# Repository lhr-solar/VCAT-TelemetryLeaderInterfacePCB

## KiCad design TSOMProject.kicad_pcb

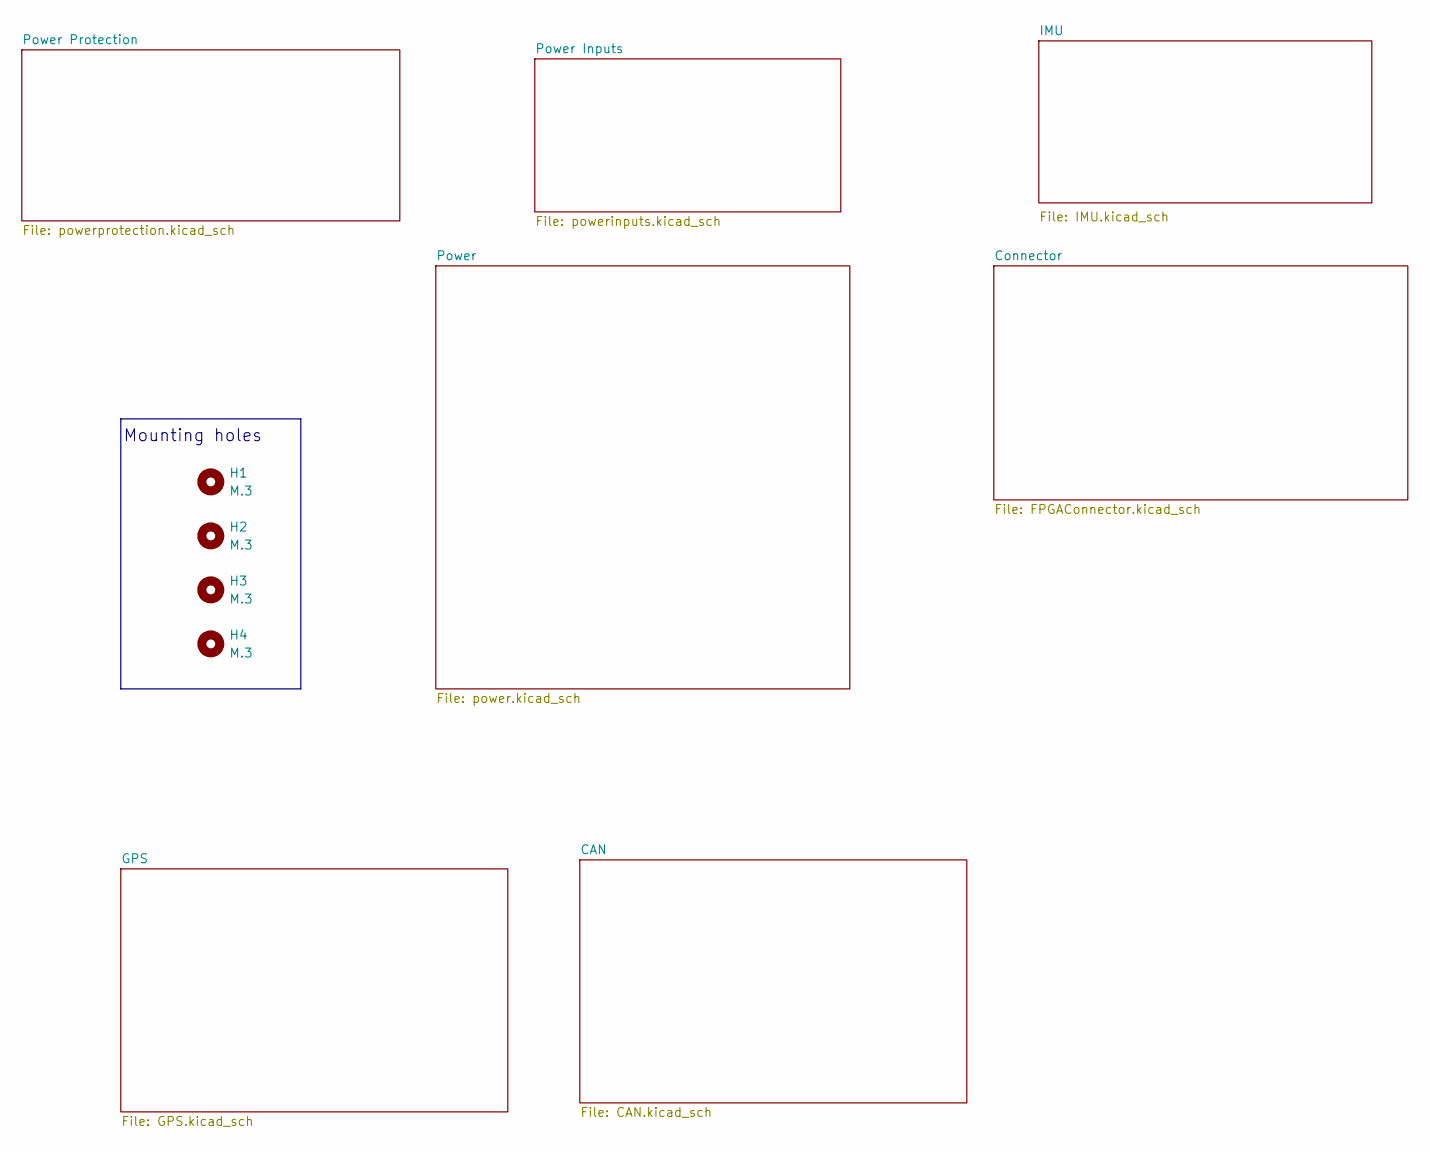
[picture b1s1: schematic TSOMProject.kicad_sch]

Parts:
H1, H2, H3, H4: M.3; MountingHole_3mm

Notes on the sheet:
Mounting holes

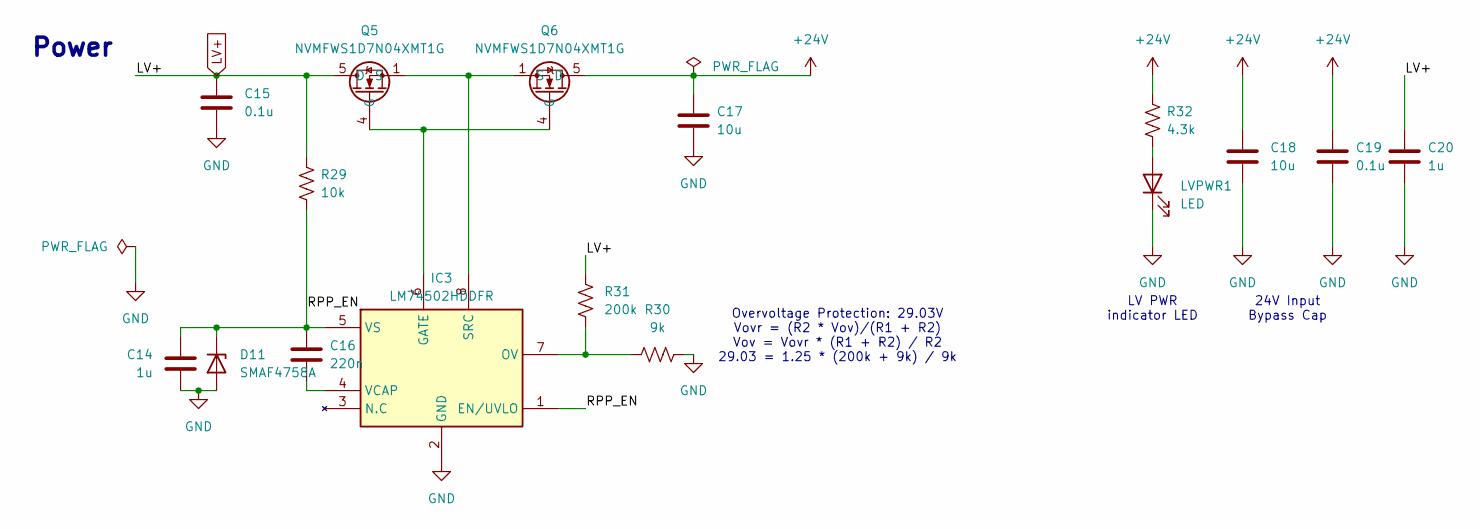
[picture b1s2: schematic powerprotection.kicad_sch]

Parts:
C14: 1u; C_0603_1608Metric_Pad1.08x0.95mm_HandSolder; Mouser Part Number 963-UMK107BJ105KA-T
C15, C19: 0.1u; C_0603_1608Metric_Pad1.08x0.95mm_HandSolder; Mouser Part Number 963-HMK107B7104KA-T
C16: 220n; C_0603_1608Metric_Pad1.08x0.95mm_HandSolder; Mouser Part Number 963-MSASU168SB7224KT
C17, C18: 10u; C_0805_2012Metric_Pad1.18x1.45mm_HandSolder; Mouser Part Number 81-GRM21BR61H106KE3K
C20: 1u; C_0603_1608Metric_Pad1.08x0.95mm_HandSolder; Mouser Part Number 963-HMK107B7104KA-T
D11: SMAF4758A; SODFL5026X125N; Mouser Part Number 833-SMAF4758A-TP
IC3: LM74502HDDFR; SOT65P280X110-8N; Mouser Part Number 595-LM74502HDDFR
LVPWR1: LED; LED_0603_1608Metric_Pad1.05x0.95mm_HandSolder; LCSC C7371904
Q5, Q6: NVMFWS1D7N04XMT1G; NVMFWS3D0P04M8LT1G; LCSC C133142
R29: 10k; R_0603_1608Metric_Pad0.98x0.95mm_HandSolder; Mouser Part Number 71-CRCW060310K0FKEI
R30: 9k; R_0603_1608Metric_Pad0.98x0.95mm_HandSolder; Mouser Part Number 594-MCT06030C9091FP5
R31: 200k; R_0603_1608Metric_Pad0.98x0.95mm_HandSolder; Mouser Part Number 594-MCT06030C2003FP5
R32: 4.3k; R_0603_1608Metric_Pad0.98x0.95mm_HandSolder; Mouser Part Number 71-CRCW0603-4.3K-E3

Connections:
+24V: C17.1, C18.1, C19.1, Q6.5 (D), Q6.6 (D), Q6.7 (D), Q6.8 (D), Q6.9 (D), R32.1; also elsewhere on the board
/Power Protection/RPP_EN: C14.2, C16.1, D11.1 (K), IC3.1 (EN/UVLO), IC3.5 (VS), R29.2
GND: C14.1, C15.2, C17.2, C18.2, C19.2, C20.2, D11.2 (A), IC3.2 (GND), LVPWR1.1 (K), R30.2; also elsewhere on the board
LV+: C15.1, C20.1, Q5.5 (D), Q5.6 (D), Q5.7 (D), Q5.8 (D), Q5.9 (D), R29.1, R31.1; also elsewhere on the board
unnamed: IC3.6 (GATE), Q5.4 (G), Q6.4 (G)
unnamed: IC3.7 (OV), R30.1, R31.2
unnamed: IC3.8 (SRC), Q5.1 (S), Q5.2 (S), Q5.3 (S), Q6.1 (S), Q6.2 (S), Q6.3 (S)
unnamed: C16.2, IC3.4 (VCAP)
unnamed: LVPWR1.2 (A), R32.2

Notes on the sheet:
24V Input Bypass Cap
LV PWR indicator LED
Overvoltage Protection: 29.03V Vovr = (R2 * Vov)/(R1 + R2) Vov = Vovr * (R1 + R2) / R2 29.03 = 1.25 * (200k + 9k) / 9k
Power

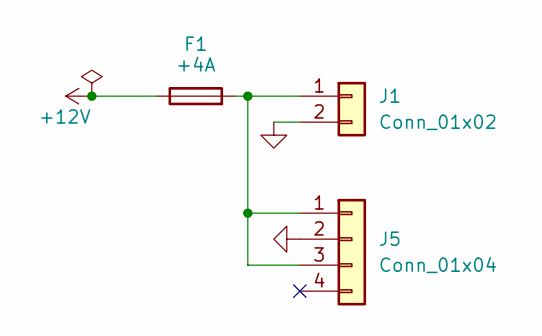
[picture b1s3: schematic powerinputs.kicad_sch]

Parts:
F1: +4A; Fuseholder_Blade_Mini_Keystone_3568
J1: Conn_01x02; Molex_Nano-Fit_105309-xx02_1x02_P2.50mm_Vertical
J5: Conn_01x04; Molex_Nano-Fit_105310-xx04_2x02_P2.50mm_Vertical

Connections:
+12V: F1.1; also elsewhere on the board
GND: J1.2, J5.2; also elsewhere on the board
unnamed: F1.2, J1.1, J5.1, J5.3

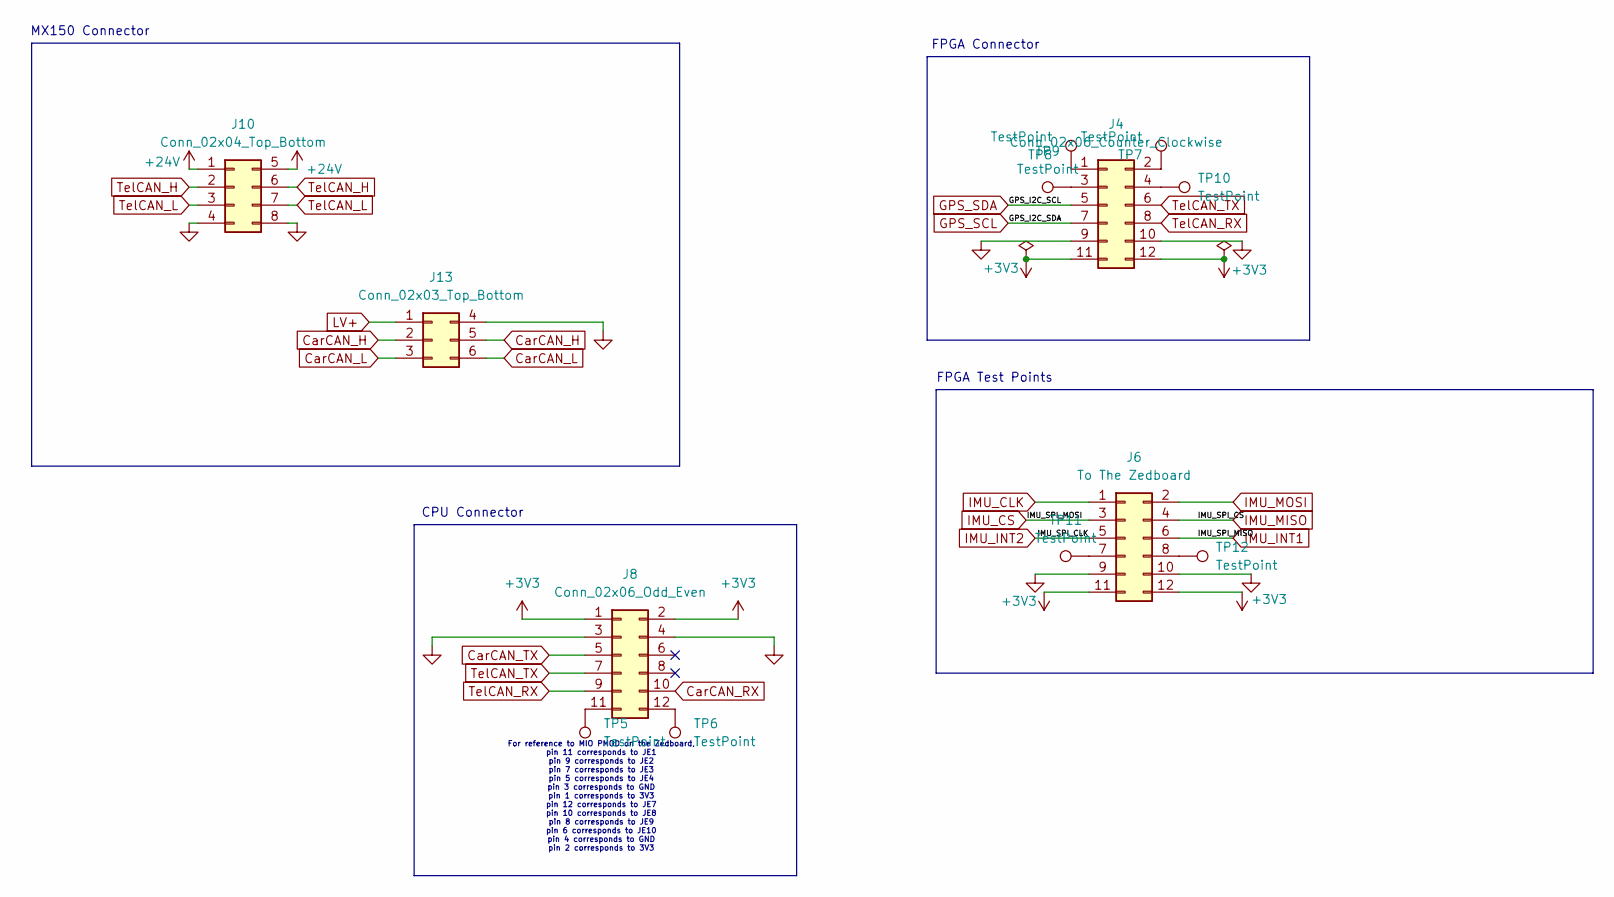
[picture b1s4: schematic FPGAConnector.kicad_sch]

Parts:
J4: Conn_02x06_Counter_Clockwise; PinHeader_2x06_P2.54mm_Vertical
J6: To The Zedboard; 2x6PmodConnectorWithZedboard
J8: Conn_02x06_Odd_Even; PinHeader_2x06_P2.54mm_Vertical
J10: Conn_02x04_Top_Bottom; Molex_Nano-Fit_105310-xx08_2x04_P2.50mm_Vertical
J13: Conn_02x03_Top_Bottom; Molex_Nano-Fit_105310-xx06_2x03_P2.50mm_Vertical
TP5, TP6, TP7, TP8, TP9, TP10, TP11, TP12: TestPoint; TestPoint_THTPad_D2.0mm_Drill1.0mm

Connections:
+3V3: J4.11, J4.12, J6.11, J6.12, J8.1, J8.2; also elsewhere on the board
+24V: J10.1, J10.5; also elsewhere on the board
CarCAN_H: J13.2, J13.5; also elsewhere on the board
CarCAN_L: J13.3, J13.6; also elsewhere on the board
CarCAN_RX: J8.10; also elsewhere on the board
CarCAN_TX: J8.5; also elsewhere on the board
GND: J4.9, J4.10, J6.9, J6.10, J8.3, J8.4, J10.4, J10.8, J13.4; also elsewhere on the board
GPS_SCL: J4.7; also elsewhere on the board
GPS_SDA: J4.5; also elsewhere on the board
IMU_CLK: J6.1; also elsewhere on the board
IMU_CS: J6.3 (Pin_2); also elsewhere on the board
IMU_INT1: J6.6; also elsewhere on the board
IMU_INT2: J6.5; also elsewhere on the board
IMU_MISO: J6.4; also elsewhere on the board
IMU_MOSI: J6.2; also elsewhere on the board
LV+: J13.1; also elsewhere on the board
unnamed: J4.1, TP8.1
unnamed: J4.2, TP7.1
unnamed: J4.3, TP9.1
unnamed: J4.4, TP10.1
unnamed: J6.7, TP11.1
unnamed: J6.8, TP12.1
unnamed: J8.11, TP5.1
unnamed: J8.12, TP6.1
TelCAN_H: J10.2, J10.6; also elsewhere on the board
TelCAN_L: J10.3, J10.7; also elsewhere on the board
TelCAN_RX: J4.8, J8.9; also elsewhere on the board
TelCAN_TX: J4.6, J8.7; also elsewhere on the board

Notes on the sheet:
MX150 Connector
CPU Connector
FPGA Test Points
For reference to MIO PMOD on the Zedboard, pin 11 corresponds to JE1 pin 9 corresponds to JE2 pin 7 corresponds to JE3 pin 5 corresponds to JE4 pin 3 corresponds to GND pin 1 corresponds to 3V3 pin 12 corresponds to JE7 pin 10 corresponds to JE8 pin 8 corresponds to JE9 pin 6 corresponds to JE10 pi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
FPGA Connector

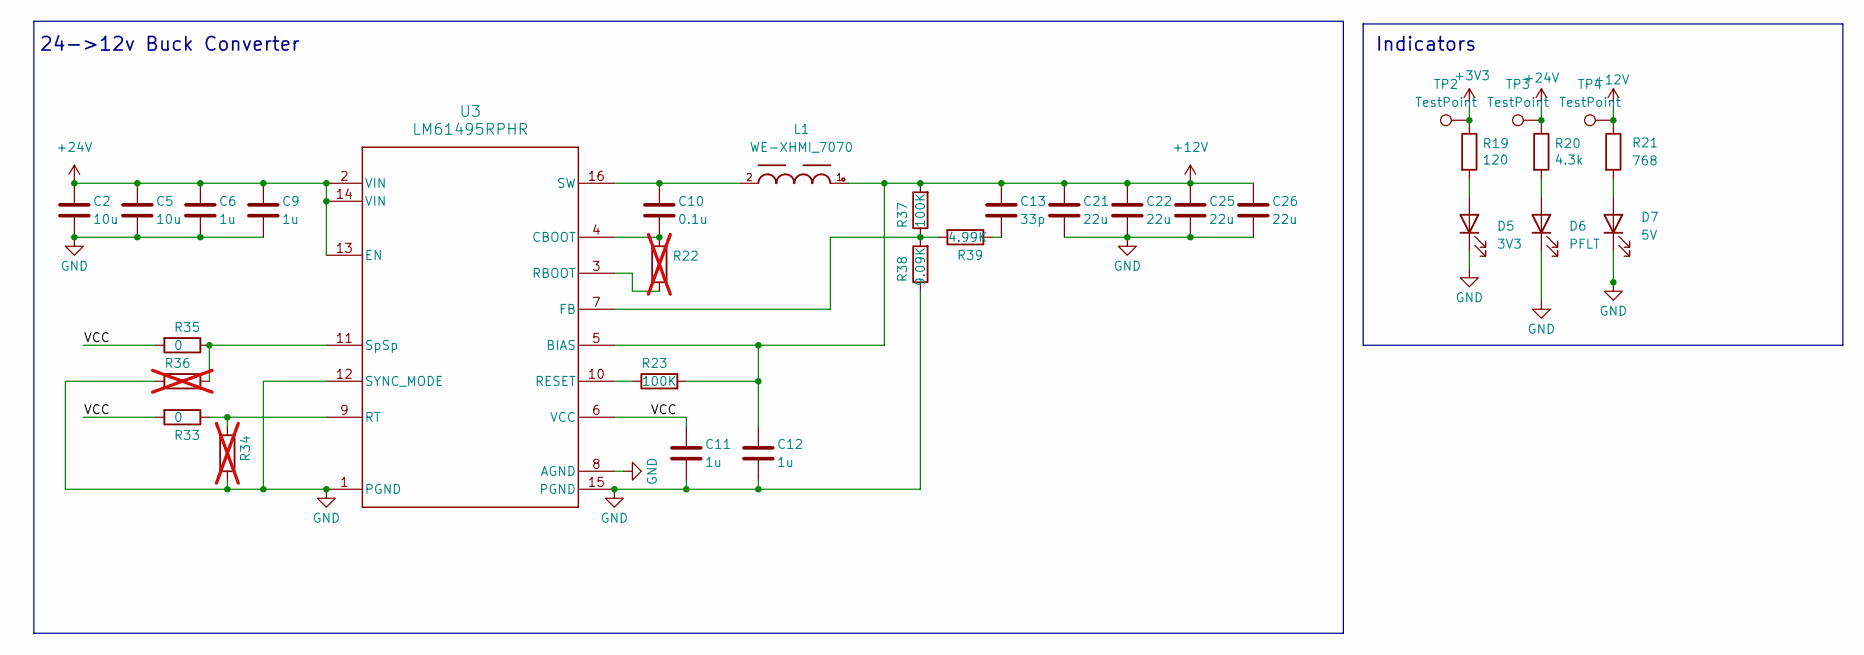
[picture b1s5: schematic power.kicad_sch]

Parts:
C2, C5: 10u; C_1206_3216Metric_Pad1.33x1.80mm_HandSolder; LCSC C7302214
C6, C9, C11, C12: 1u; C_0603_1608Metric_Pad1.08x0.95mm_HandSolder; LCSC C15849
C10: 0.1u; C_0603_1608Metric_Pad1.08x0.95mm_HandSolder; LCSC C14663
C13: 33p; C_0603_1608Metric_Pad1.08x0.95mm_HandSolder; LCSC C1663
C21, C22, C25, C26: 22u; C_1210_3225Metric_Pad1.33x2.70mm_HandSolder; LCSC C21397
D5: 3V3; LED_0603_1608Metric_Pad1.05x0.95mm_HandSolder; Mouser Part Number XL-1608UBC-06A
D6: PFLT; LED_0603_1608Metric_Pad1.05x0.95mm_HandSolder; Mouser Part Number XL-1608UBC-06A
D7: 5V; LED_0603_1608Metric_Pad1.05x0.95mm_HandSolder; Mouser Part Number XL-1608UBC-06A
L1: WE-XHMI_7070
R19: 120; R_0603_1608Metric_Pad0.98x0.95mm_HandSolder; Mouser Part Number CRCW0603120RFKEC
R20: 4.3k; R_0603_1608Metric_Pad0.98x0.95mm_HandSolder; Mouser Part Number CRCW06034K30FKTA
R21: 768; R_0603_1608Metric_Pad0.98x0.95mm_HandSolder; Mouser Part Number CRCW0603768RFKEA
R22, R34, R36: R_0603_1608Metric_Pad0.98x0.95mm_HandSolder; Mouser Part Number CRCW0603120RFKEC; not fitted
R23, R37: 100K; R_0603_1608Metric_Pad0.98x0.95mm_HandSolder; Mouser Part Number CRCW0603120RFKEC
R33, R35: 0; R_0603_1608Metric_Pad0.98x0.95mm_HandSolder; Mouser Part Number CRCW0603120RFKEC
R38: 9.09K; R_0603_1608Metric_Pad0.98x0.95mm_HandSolder; Mouser Part Number CRCW0603120RFKEC
R39: 4.99K; R_0603_1608Metric_Pad0.98x0.95mm_HandSolder; Mouser Part Number CRCW0603120RFKEC
TP2, TP3, TP4: TestPoint; TestPoint_THTPad_D2.0mm_Drill1.0mm
U3: LM61495RPHR; LCSC C2943584

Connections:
+3V3: R19.1, TP2.1; also elsewhere on the board
+12V: C12.1, C13.1, C21.1, C22.1, C25.1, C26.1, L1.1, R21.1, R23.2, R37.2, TP4.1, U3.5 (BIAS); also elsewhere on the board
+24V: C2.1, C5.1, C6.1, C9.1, R20.1, TP3.1, U3.2 (VIN), U3.13 (EN), U3.14 (VIN); also elsewhere on the board
/Power/VCC: C11.1, R33.2, R35.2, U3.6 (VCC)
GND: C2.2, C5.2, C6.2, C9.2, C11.2, C12.2, C21.2, C22.2, C25.2, C26.2, D5.1 (K), D6.1 (K), D7.1 (K), R34.2, R36.1, R38.1, U3.1 (PGND), U3.8 (AGND), U3.12 (SYNC_MODE), U3.15 (PGND); also elsewhere on the board
unnamed: C13.2, R39.1
unnamed: D5.2 (A), R19.2
unnamed: D6.2 (A), R20.2
unnamed: D7.2 (A), R21.2
unnamed: C10.2, R22.1, U3.4 (CBOOT)
unnamed: R37.1, R38.2, R39.2, U3.7 (FB)
unnamed: R22.2, U3.3 (RBOOT)
unnamed: R23.1, U3.10 (RESET)
unnamed: R33.1, R34.1, U3.9 (RT)
unnamed: C10.1, L1.2, U3.16 (SW)
unnamed: R35.1, R36.2, U3.11 (SpSp)

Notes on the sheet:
Indicators
24->12v Buck Converter

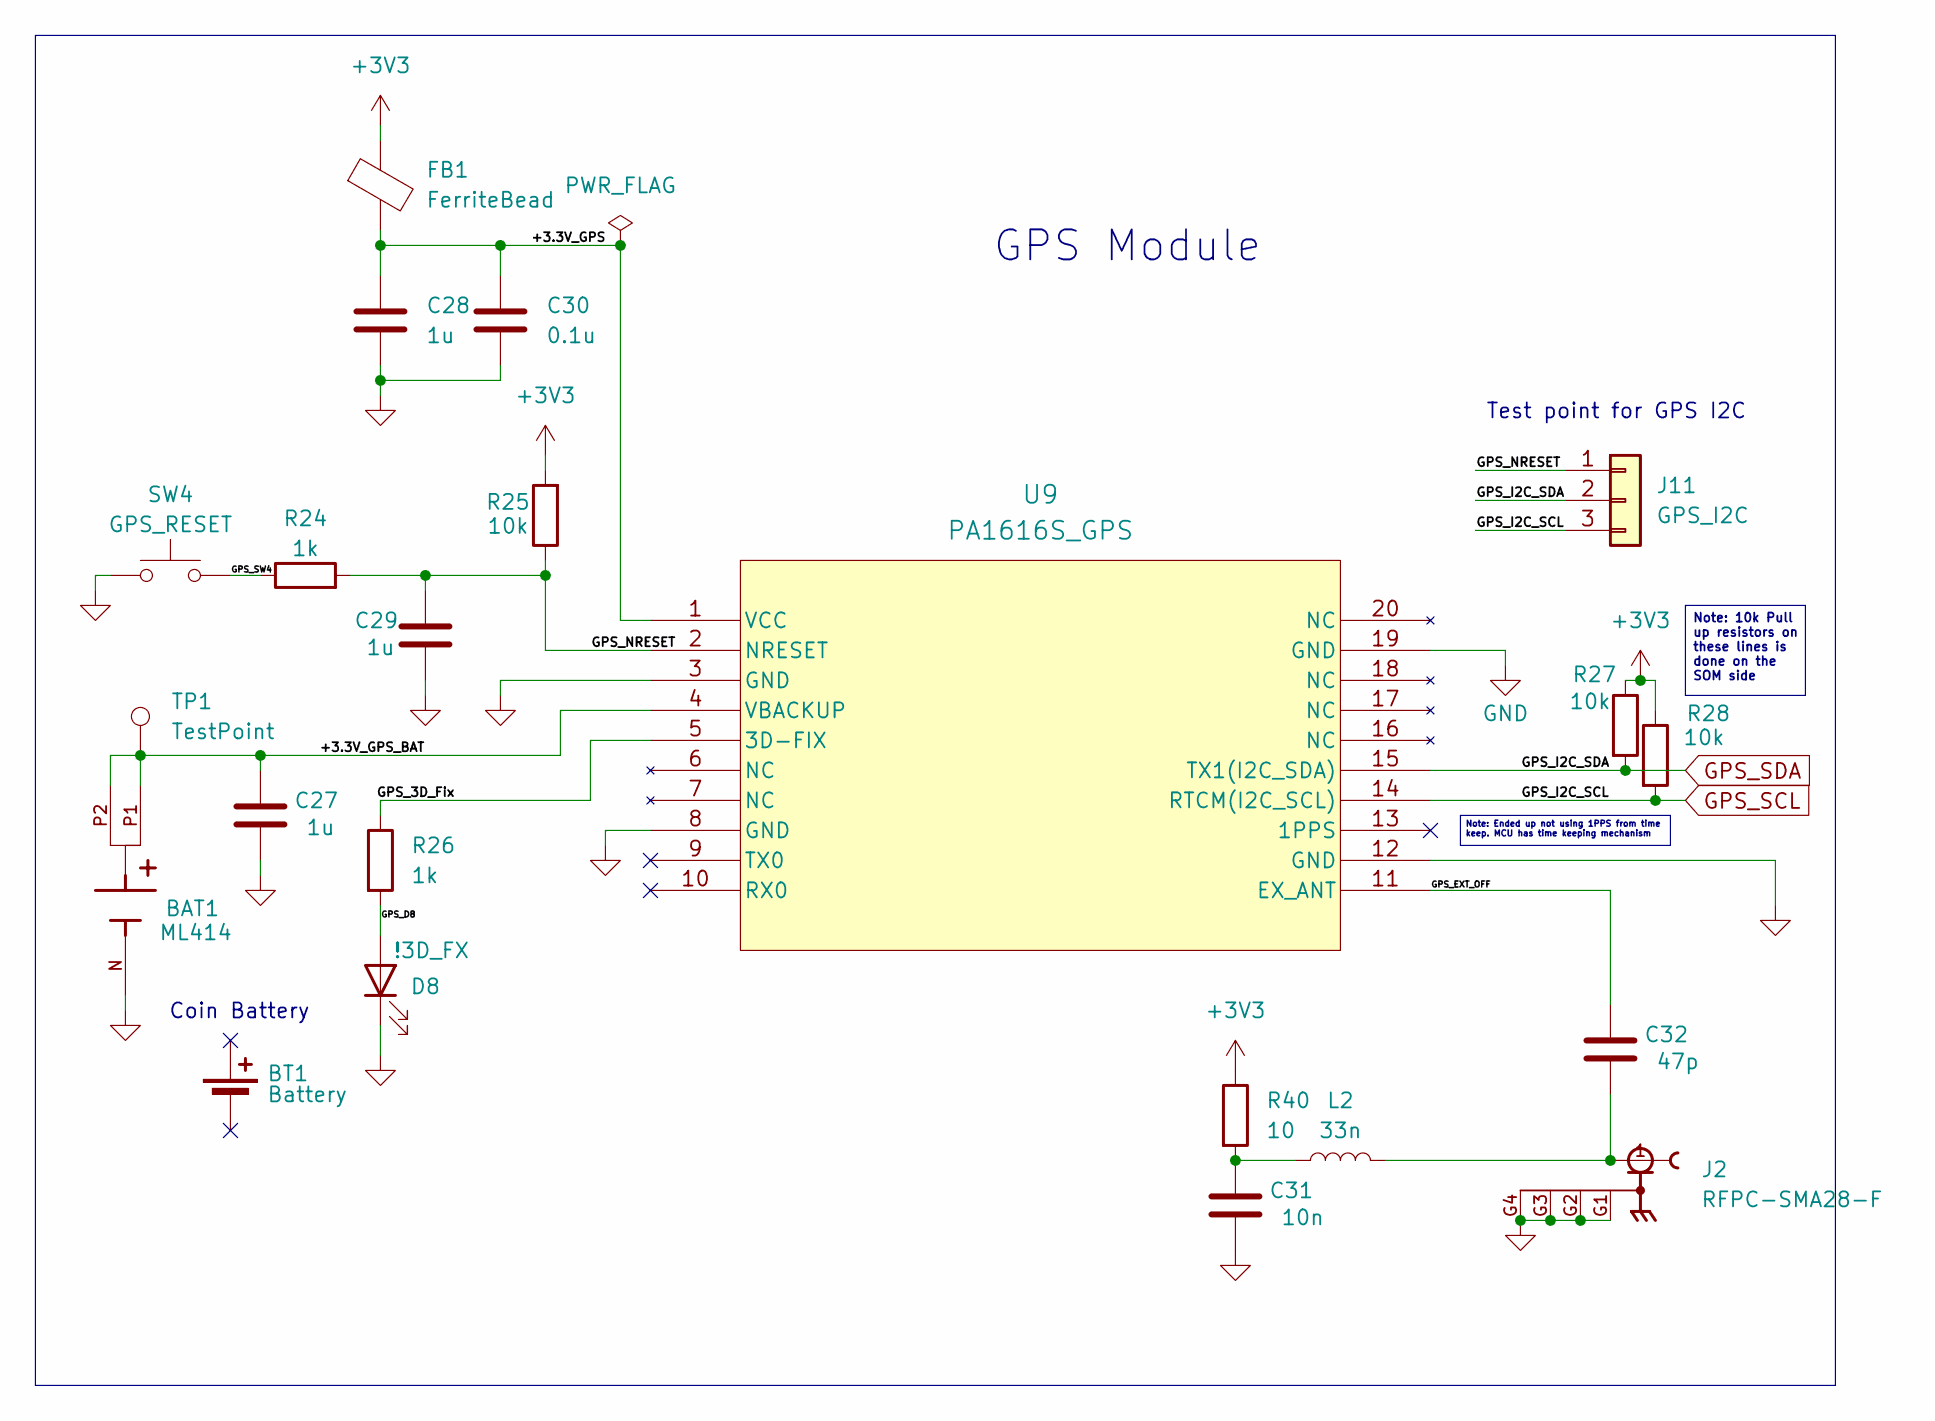
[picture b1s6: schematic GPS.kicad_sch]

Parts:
BAT1: ML414; BAT_2994TR; Mouser Part Number 534-2994TR
BT1: Battery; NA; Mouser Part Number 628-MS414GE
C27, C28, C29: 1u; C_0603_1608Metric_Pad1.08x0.95mm_HandSolder; Mouser Part Number 80-C0805C105J4RACLR
C30: 0.1u; C_0603_1608Metric_Pad1.08x0.95mm_HandSolder; Mouser Part Number 80-C0805C104M5R
C31: 10n; C_0603_1608Metric_Pad1.08x0.95mm_HandSolder; Mouser Part Number 80-C0805C105J4RACLR
C32: 47p; C_0603_1608Metric_Pad1.08x0.95mm_HandSolder; Mouser Part Number 80-C0805C105J4RACLR
D8: !3D_FX; LED_0603_1608Metric_Pad1.05x0.95mm_HandSolder; Mouser Part Number 604-APTD2012LCGCK
FB1: FerriteBead; L_0603_1608Metric_Pad1.05x0.95mm_HandSolder; Mouser Part Number 81-BLM15BD601SN1D
J2: RFPC-SMA28-F; GRADCONN_RFPC-SMA28-F; PARTREV 1.0
J11: GPS_I2C; PinHeader_1x03_P2.54mm_Vertical; Mouser Part Number 538-22-28-4035
L2: 33n; L_0603_1608Metric_Pad1.05x0.95mm_HandSolder; LCSC C86068
R24, R26: 1k; R_0603_1608Metric_Pad0.98x0.95mm_HandSolder; Mouser Part Number 71-CRCW08051K00FKEAC
R25: 10k; R_0603_1608Metric_Pad0.98x0.95mm_HandSolder; Mouser Part Number 71-CRCW0805-10K-E3
R27, R28: 10k; R_0603_1608Metric_Pad0.98x0.95mm_HandSolder; LCSC C25804
R40: 10; R_0603_1608Metric_Pad0.98x0.95mm_HandSolder; Mouser Part Number 71-CRCW08051K00FKEAC
SW4: GPS_RESET; SW_SPST_B3SL-1002P; Mouser Part Number 653-B3SL-1002P
TP1: TestPoint; TestPoint_THTPad_D2.0mm_Drill1.0mm
U9: PA1616S_GPS; PA1616S_ADA

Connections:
+3V3: FB1.1, R25.2, R27.1, R28.1, R40.1; also elsewhere on the board
/GPS/+3.3V_GPS: C28.1, C30.1, FB1.2, U9.1 (VCC)
/GPS/+3.3V_GPS_BAT: BAT1.P1, BAT1.P2, C27.1, TP1.1, U9.4 (VBACKUP)
/GPS/GPS_3D_Fix: R26.1, U9.5 (3D-FIX)
/GPS/GPS_D8: D8.2 (A), R26.2
/GPS/GPS_EXT_OFF: C32.1, U9.11 (EX_ANT)
/GPS/GPS_NRESET: C29.1, J11.1, R24.2, R25.1, U9.2 (NRESET)
/GPS/GPS_SW4: R24.1, SW4.2
GND: BAT1.N, C27.2, C28.2, C29.2, C30.2, C31.2, D8.1 (K), J2.G1, J2.G2, J2.G3, J2.G4, SW4.1, U9.3 (GND), U9.8 (GND), U9.12 (GND), U9.19 (GND); also elsewhere on the board
GPS_SCL: J11.3, R28.2, U9.14 (RTCM(I2C_SCL)); also elsewhere on the board
GPS_SDA: J11.2, R27.2, U9.15 (TX1(I2C_SDA)); also elsewhere on the board
unnamed: C31.1, L2.1, R40.2
unnamed: C32.2, J2.1, L2.2

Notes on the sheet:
GPS Module
Coin Battery
Test point for GPS I2C
Note: 10k Pull up resistors on these lines is done on the SOM side
Note: Ended up not using 1PPS from time keep. MCU has time keeping mechanism

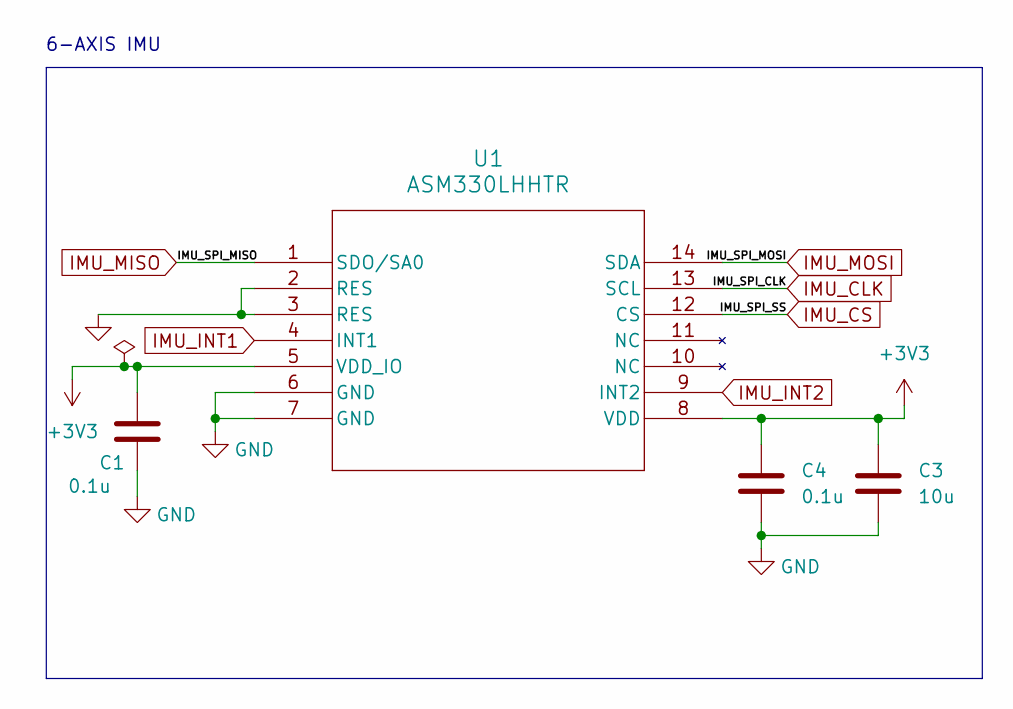
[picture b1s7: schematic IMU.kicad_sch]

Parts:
C1, C4: 0.1u; C_0603_1608Metric_Pad1.08x0.95mm_HandSolder
C3: 10u; C_0805_2012Metric_Pad1.18x1.45mm_HandSolder
U1: ASM330LHHTR; LSM6DS3USTR

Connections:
+3V3: C1.1, C3.1, C4.1, U1.5 (VDD_IO), U1.8 (VDD); also elsewhere on the board
GND: C1.2, C3.2, C4.2, U1.2 (RES), U1.3 (RES), U1.6 (GND), U1.7 (GND); also elsewhere on the board
IMU_CLK: U1.13 (SCL); also elsewhere on the board
IMU_CS: U1.12 (CS); also elsewhere on the board
IMU_INT1: U1.4 (INT1); also elsewhere on the board
IMU_INT2: U1.9 (INT2); also elsewhere on the board
IMU_MISO: U1.1 (SDO/SA0); also elsewhere on the board
IMU_MOSI: U1.14 (SDA); also elsewhere on the board

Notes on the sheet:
6-AXIS IMU

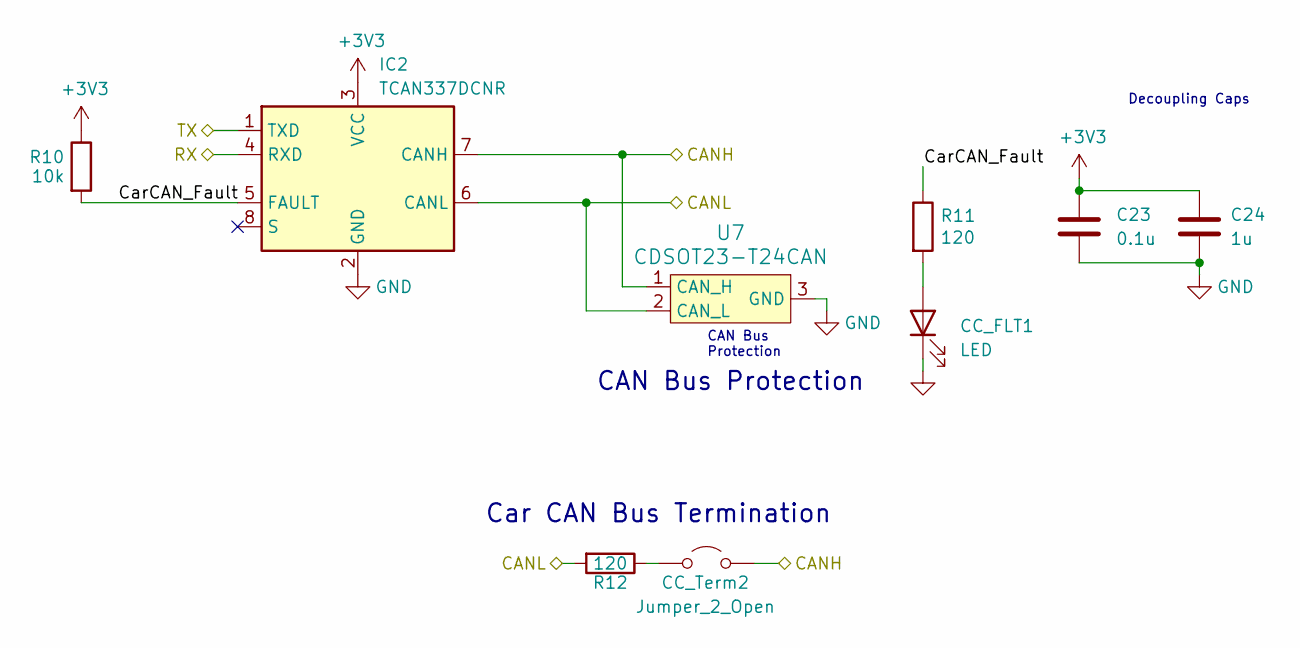
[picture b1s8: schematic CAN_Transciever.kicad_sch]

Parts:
C23: 0.1u; C_0603_1608Metric_Pad1.08x0.95mm_HandSolder; Mouser Part Number MLASH168SB7104KTNA01
C24: 1u; C_0603_1608Metric_Pad1.08x0.95mm_HandSolder; Mouser Part Number MLASU168SB5105KTNA01
CC_FLT1: LED; LED_0603_1608Metric_Pad1.05x0.95mm_HandSolder; Mouser Part Number 604-APTD2012LCGCK
CC_Term2: Jumper_2_Open; PinHeader_1x02_P2.54mm_Vertical
IC2: TCAN337DCNR; Mouser Part Number 595-TCAN337DCNR
R10: 10k; R_0603_1608Metric_Pad0.98x0.95mm_HandSolder; Mouser Part Number CRCW060310K0FKEI
R11: 120; R_0603_1608Metric_Pad0.98x0.95mm_HandSolder; Mouser Part Number CRCW06032K10FKEA
R12: 120; R_0603_1608Metric_Pad0.98x0.95mm_HandSolder; Mouser Part Number CRCW0603120RFKEC
U7: CDSOT23-T24CAN; Mouser Part Number CDSOT23-T24CAN

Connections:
+3V3: C23.1, C24.1, IC2.3 (VCC), R10.1; also elsewhere on the board
/CAN/CarCAN Transciever/CarCAN_Fault: IC2.5 (FAULT), R10.2, R11.1
CarCAN_H: CC_Term2.2 (B), IC2.7 (CANH), U7.1 (CAN_H); also elsewhere on the board
CarCAN_L: IC2.6 (CANL), R12.2, U7.2 (CAN_L); also elsewhere on the board
CarCAN_RX: IC2.4 (RXD); also elsewhere on the board
CarCAN_TX: IC2.1 (TXD); also elsewhere on the board
GND: C23.2, C24.2, CC_FLT1.1 (K), IC2.2 (GND), U7.3 (GND); also elsewhere on the board
unnamed: CC_FLT1.2 (A), R11.2
unnamed: CC_Term2.1 (A), R12.1

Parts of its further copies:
C7: 0.1u; C_0603_1608Metric_Pad1.08x0.95mm_HandSolder; Mouser Part Number MLASH168SB7104KTNA01
C8: 1u; C_0603_1608Metric_Pad1.08x0.95mm_HandSolder; Mouser Part Number MLASU168SB5105KTNA01
CC_FLT2: LED; LED_0603_1608Metric_Pad1.05x0.95mm_HandSolder; Mouser Part Number 604-APTD2012LCGCK
CC_Term1: Jumper_2_Open; PinHeader_1x02_P2.54mm_Vertical
IC1: TCAN337DCNR; Mouser Part Number 595-TCAN337DCNR
R1: 10k; R_0603_1608Metric_Pad0.98x0.95mm_HandSolder; Mouser Part Number CRCW060310K0FKEI
R2: 120; R_0603_1608Metric_Pad0.98x0.95mm_HandSolder; Mouser Part Number CRCW06032K10FKEA
R3: 120; R_0603_1608Metric_Pad0.98x0.95mm_HandSolder; Mouser Part Number CRCW0603120RFKEC
U2: CDSOT23-T24CAN; Mouser Part Number CDSOT23-T24CAN

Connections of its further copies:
+3V3: C7.1, C8.1, IC1.3 (VCC), R1.1; also elsewhere on the board
/CAN/TelCAN Transciever/CarCAN_Fault: IC1.5 (FAULT), R1.2, R2.1
GND: C7.2, C8.2, CC_FLT2.1 (K), IC1.2 (GND), U2.3 (GND); also elsewhere on the board
unnamed: CC_FLT2.2 (A), R2.2
unnamed: CC_Term1.1 (A), R3.1
TelCAN_H: CC_Term1.2 (B), IC1.7 (CANH), U2.1 (CAN_H); also elsewhere on the board
TelCAN_L: IC1.6 (CANL), R3.2, U2.2 (CAN_L); also elsewhere on the board
TelCAN_RX: IC1.4 (RXD); also elsewhere on the board
TelCAN_TX: IC1.1 (TXD); also elsewhere on the board

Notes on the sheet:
Decoupling Caps
CAN Bus Protection
CAN Bus Protection
Car CAN Bus Termination

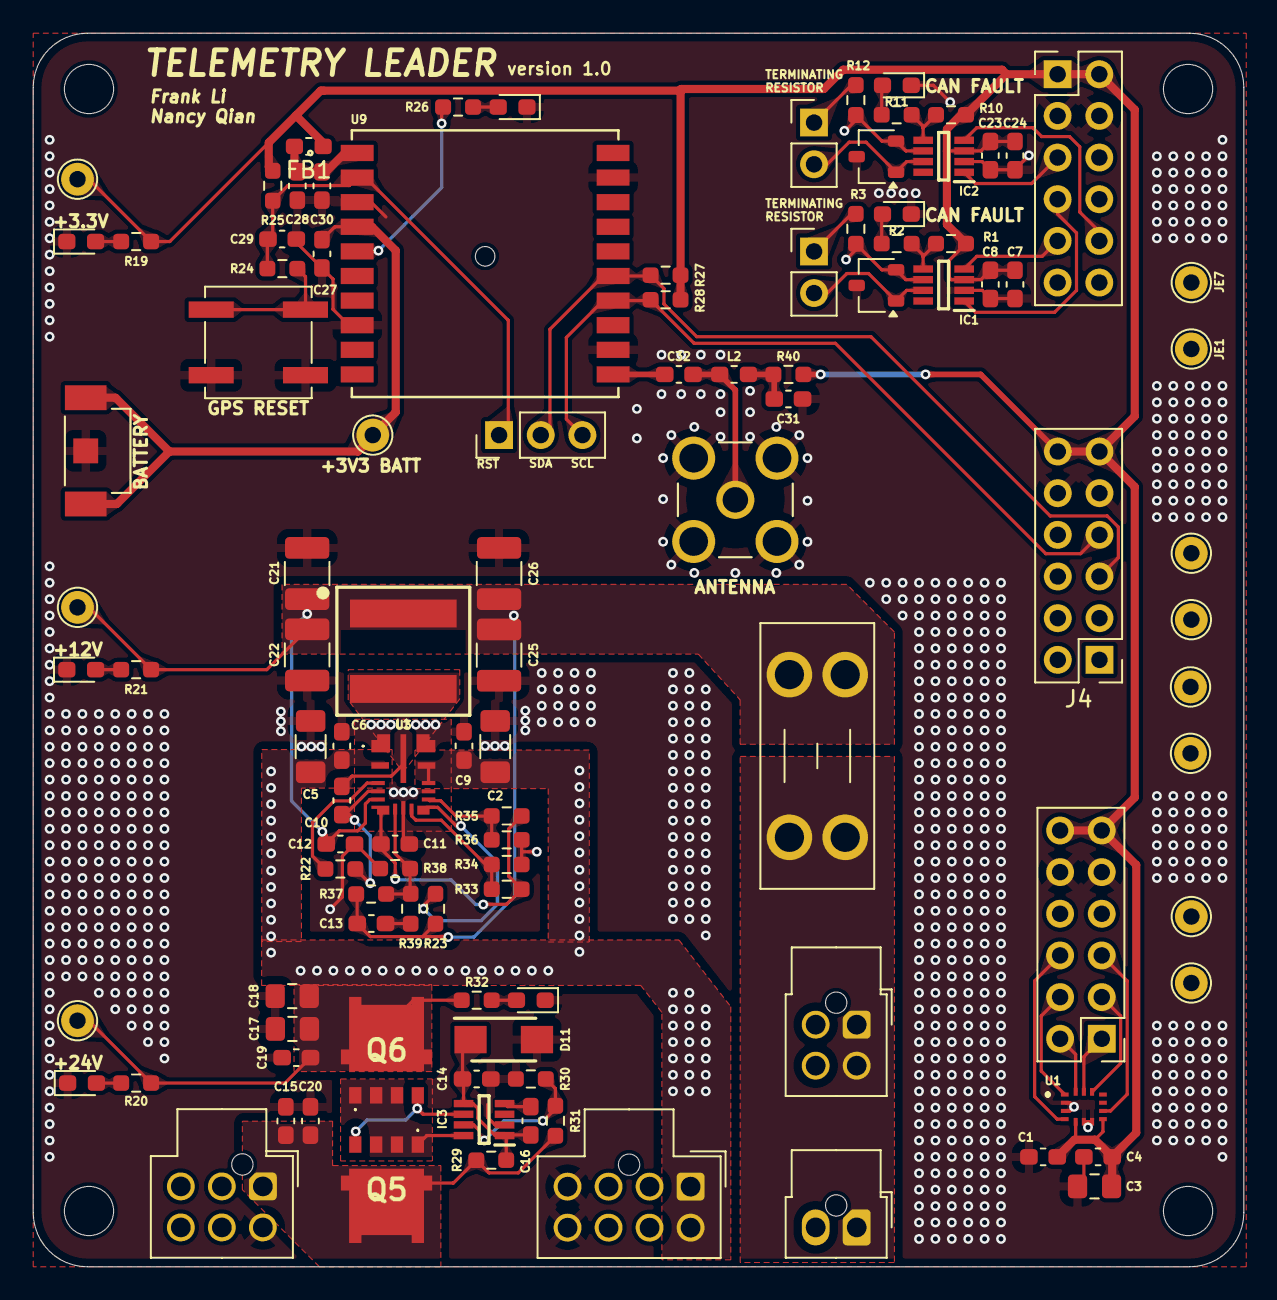
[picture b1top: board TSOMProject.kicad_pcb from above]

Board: 4 copper layers, 73.8 x 75.2 mm, 111 parts (0 on the bottom side), 63 nets.

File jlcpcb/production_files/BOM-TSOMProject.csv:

Comment,Designator,Footprint,LCSC,Quantity
!3D_FX,D8,LED_0603_1608Metric_Pad1.05x0.95mm_HandSolder,C7371904,1
+4A,F1,Fuseholder_Blade_Mini_Keystone_3568,C5249699,1
0,"R33,R35",R_0603_1608Metric_Pad0.98x0.95mm_HandSolder,C21189,2
0.1u,"C1,C10,C15,C19,C23,C30,C4,C7",C_0603_1608Metric_Pad1.08x0.95mm_HandSolder,C14663,8
10,R40,R_0603_1608Metric_Pad0.98x0.95mm_HandSolder,C22859,1
100K,"R23,R37",R_0603_1608Metric_Pad0.98x0.95mm_HandSolder,C25803,2
10k,"R1,R10,R25,R27,R28,R29",R_0603_1608Metric_Pad0.98x0.95mm_HandSolder,C25804,6
10n,C31,C_0603_1608Metric_Pad1.08x0.95mm_HandSolder,C57112,1
10u,"C17,C18,C3",C_0805_2012Metric_Pad1.18x1.45mm_HandSolder,C440198,3
10u,"C2,C5",C_1206_3216Metric_Pad1.33x1.80mm_HandSolder,C7302214,2
120,"R11,R12,R19,R2,R3",R_0603_1608Metric_Pad0.98x0.95mm_HandSolder,C22787,5
1k,"R24,R26",R_0603_1608Metric_Pad0.98x0.95mm_HandSolder,C21190,2
1u,"C11,C12,C14,C20,C24,C27,C28,C29,C6,C8,C9",C_0603_1608Metric_Pad1.08x0.95mm_HandSolder,C15849,11
200k,R31,R_0603_1608Metric_Pad0.98x0.95mm_HandSolder,C25811,1
220n,C16,C_0603_1608Metric_Pad1.08x0.95mm_HandSolder,C64705,1
22u,"C21,C22,C25,C26",C_1210_3225Metric_Pad1.33x2.70mm_HandSolder,C21397,4
33n,L2,L_0603_1608Metric_Pad1.05x0.95mm_HandSolder,C86068,1
33p,C13,C_0603_1608Metric_Pad1.08x0.95mm_HandSolder,C1663,1
3V3,D5,LED_0603_1608Metric_Pad1.05x0.95mm_HandSolder,C7371904,1
4.3k,"R20,R32",R_0603_1608Metric_Pad0.98x0.95mm_HandSolder,C2907165,2
4.99K,R39,R_0603_1608Metric_Pad0.98x0.95mm_HandSolder,C23046,1
47p,C32,C_0603_1608Metric_Pad1.08x0.95mm_HandSolder,C1671,1
5V,D7,LED_0603_1608Metric_Pad1.05x0.95mm_HandSolder,C7371904,1
768,R21,R_0603_1608Metric_Pad0.98x0.95mm_HandSolder,C23108,1
9.09K,R38,R_0603_1608Metric_Pad0.98x0.95mm_HandSolder,C185301,1
9k,R30,R_0603_1608Metric_Pad0.98x0.95mm_HandSolder,C13259,1
ASM330LHHTR,U1,LSM6DS3USTR,C459826,1
CDSOT23-T24CAN,"U2,U7",CDSOT23-T24CAN,C2959841,2
LED,"CC_FLT1,CC_FLT2,LVPWR1",LED_0603_1608Metric_Pad1.05x0.95mm_HandSolder,C7371904,3
LM61495RPHR,U3,LM61495RPHR,C2943584,1
LM74502HDDFR,IC3,SOT65P280X110-8N,C5219202,1
NVMFWS1D7N04XMT1G,"Q5,Q6",NVMFWS3D0P04M8LT1G,C133142,2
PFLT,D6,LED_0603_1608Metric_Pad1.05x0.95mm_HandSolder,C7371904,1
SMAF4758A,D11,SODFL5026X125N,C183490,1
PA1616S_GPS,U9,PA1616S_ADA,,1
ML414,BAT1,BAT_2994TR,,1
Conn_02x03_Top_Bottom,J13,Molex_Nano-Fit_105310-xx06_2x03_P2.50mm_Vertical,,1
TestPoint,TP4,TestPoint_THTPad_D2.0mm_Drill1.0mm,,1
GPS_RESET,SW4,SW_SPST_B3SL-1002P,,1
Conn_02x06_Counter_Clockwise,J4,PinHeader_2x06_P2.54mm_Vertical,,1
To The Zedboard,J6,2x6PmodConnectorWithZedboard,,1
GPS_I2C,J11,PinHeader_1x03_P2.54mm_Vertical,,1
TestPoint,TP2,TestPoint_THTPad_D2.0mm_Drill1.0mm,,1
~,,R_0603_1608Metric_Pad0.98x0.95mm_HandSolder,,0
Conn_02x04_Top_Bottom,J10,Molex_Nano-Fit_105310-xx08_2x04_P2.50mm_Vertical,,1
TCAN337DCNR,IC2,TCAN337DCNR,,1
WE-XHMI_7070,L1,WE-XHMI_7070,,1
Conn_01x02,J1,Molex_Nano-Fit_105309-xx02_1x02_P2.50mm_Vertical,,1
TestPoint,TP1,TestPoint_THTPad_D2.0mm_Drill1.0mm,,1
Conn_02x06_Odd_Even,J8,PinHeader_2x06_P2.54mm_Vertical,,1
TCAN337DCNR,IC1,TCAN337DCNR,,1
~,,R_0603_1608Metric_Pad0.98x0.95mm_HandSolder,,0
FerriteBead,FB1,L_0603_1608Metric_Pad1.05x0.95mm_HandSolder,,1
~,,R_0603_1608Metric_Pad0.98x0.95mm_HandSolder,,0
TestPoint,TP3,TestPoint_THTPad_D2.0mm_Drill1.0mm,,1
TestPoint,TP9,TestPoint_THTPad_D2.0mm_Drill1.0mm,,1
TestPoint,TP10,TestPoint_THTPad_D2.0mm_Drill1.0mm,,1
TestPoint,TP11,TestPoint_THTPad_D2.0mm_Drill1.0mm,,1
TestPoint,TP7,TestPoint_THTPad_D2.0mm_Drill1.0mm,,1
TestPoint,TP12,TestPoint_THTPad_D2.0mm_Drill1.0mm,,1
TestPoint,TP5,TestPoint_THTPad_D2.0mm_Drill1.0mm,,1
RFPC-SMA28-F,J2,GRADCONN_RFPC-SMA28-F,,1
TestPoint,TP6,TestPoint_THTPad_D2.0mm_Drill1.0mm,,1
Conn_01x04,J5,Molex_Nano-Fit_105310-xx04_2x02_P2.50mm_Vertical,,1
TestPoint,TP8,TestPoint_THTPad_D2.0mm_Drill1.0mm,,1

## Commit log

2026-01-01 tsom sch
2026-01-11 power/connectors
2026-01-15 remove bak/lck
2026-01-24 fix errors schem
2026-01-31 fin schematic
2026-01-31 only da inductor
2026-01-31 start layout
2026-02-07 im cooked
2026-02-07 Clean up tracked files and apply .gitignore
2026-02-09 more layout
2026-02-11 stuff
2026-02-11 Fixed sub-repo issue and merged files
2026-02-11 Final cleanup: removed autosaves and metadata
2026-02-11 hiuhcahscks
2026-02-14 delete
2026-02-21 comm
2026-03-16 deleting everything
2026-03-16 reorganized repo, fixed sch, nearly complete layout
2026-03-16 done antenna
2026-03-16 did some stuff
2026-03-16 mika changes
2026-03-16 gerb
